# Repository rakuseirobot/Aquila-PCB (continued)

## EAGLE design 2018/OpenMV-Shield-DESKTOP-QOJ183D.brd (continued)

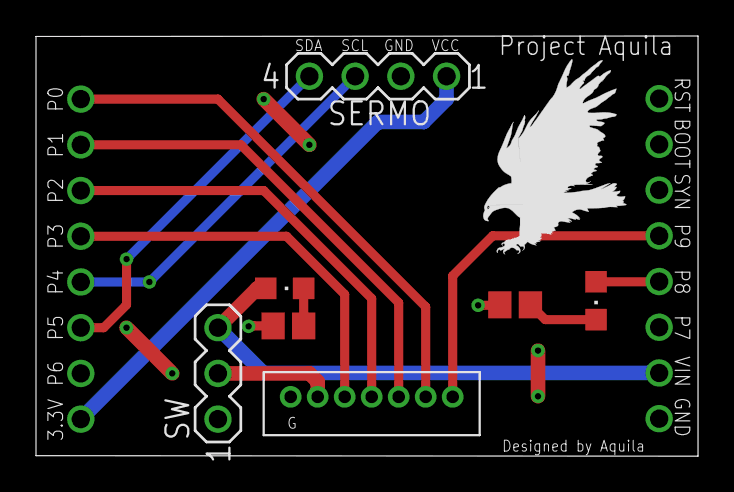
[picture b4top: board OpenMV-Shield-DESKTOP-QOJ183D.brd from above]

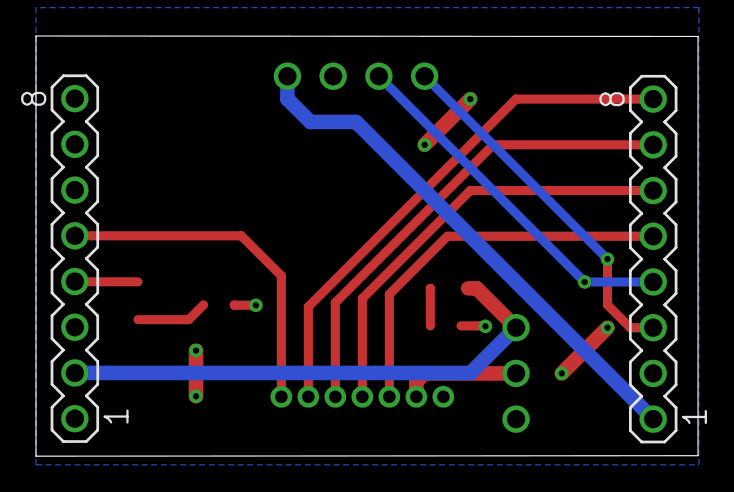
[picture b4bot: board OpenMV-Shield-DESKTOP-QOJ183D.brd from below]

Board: 2 copper layers, 36.8 x 23.3 mm, 10 parts (2 on the bottom side), 14 nets.

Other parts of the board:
U$1: EAGLE-PLC-8MM

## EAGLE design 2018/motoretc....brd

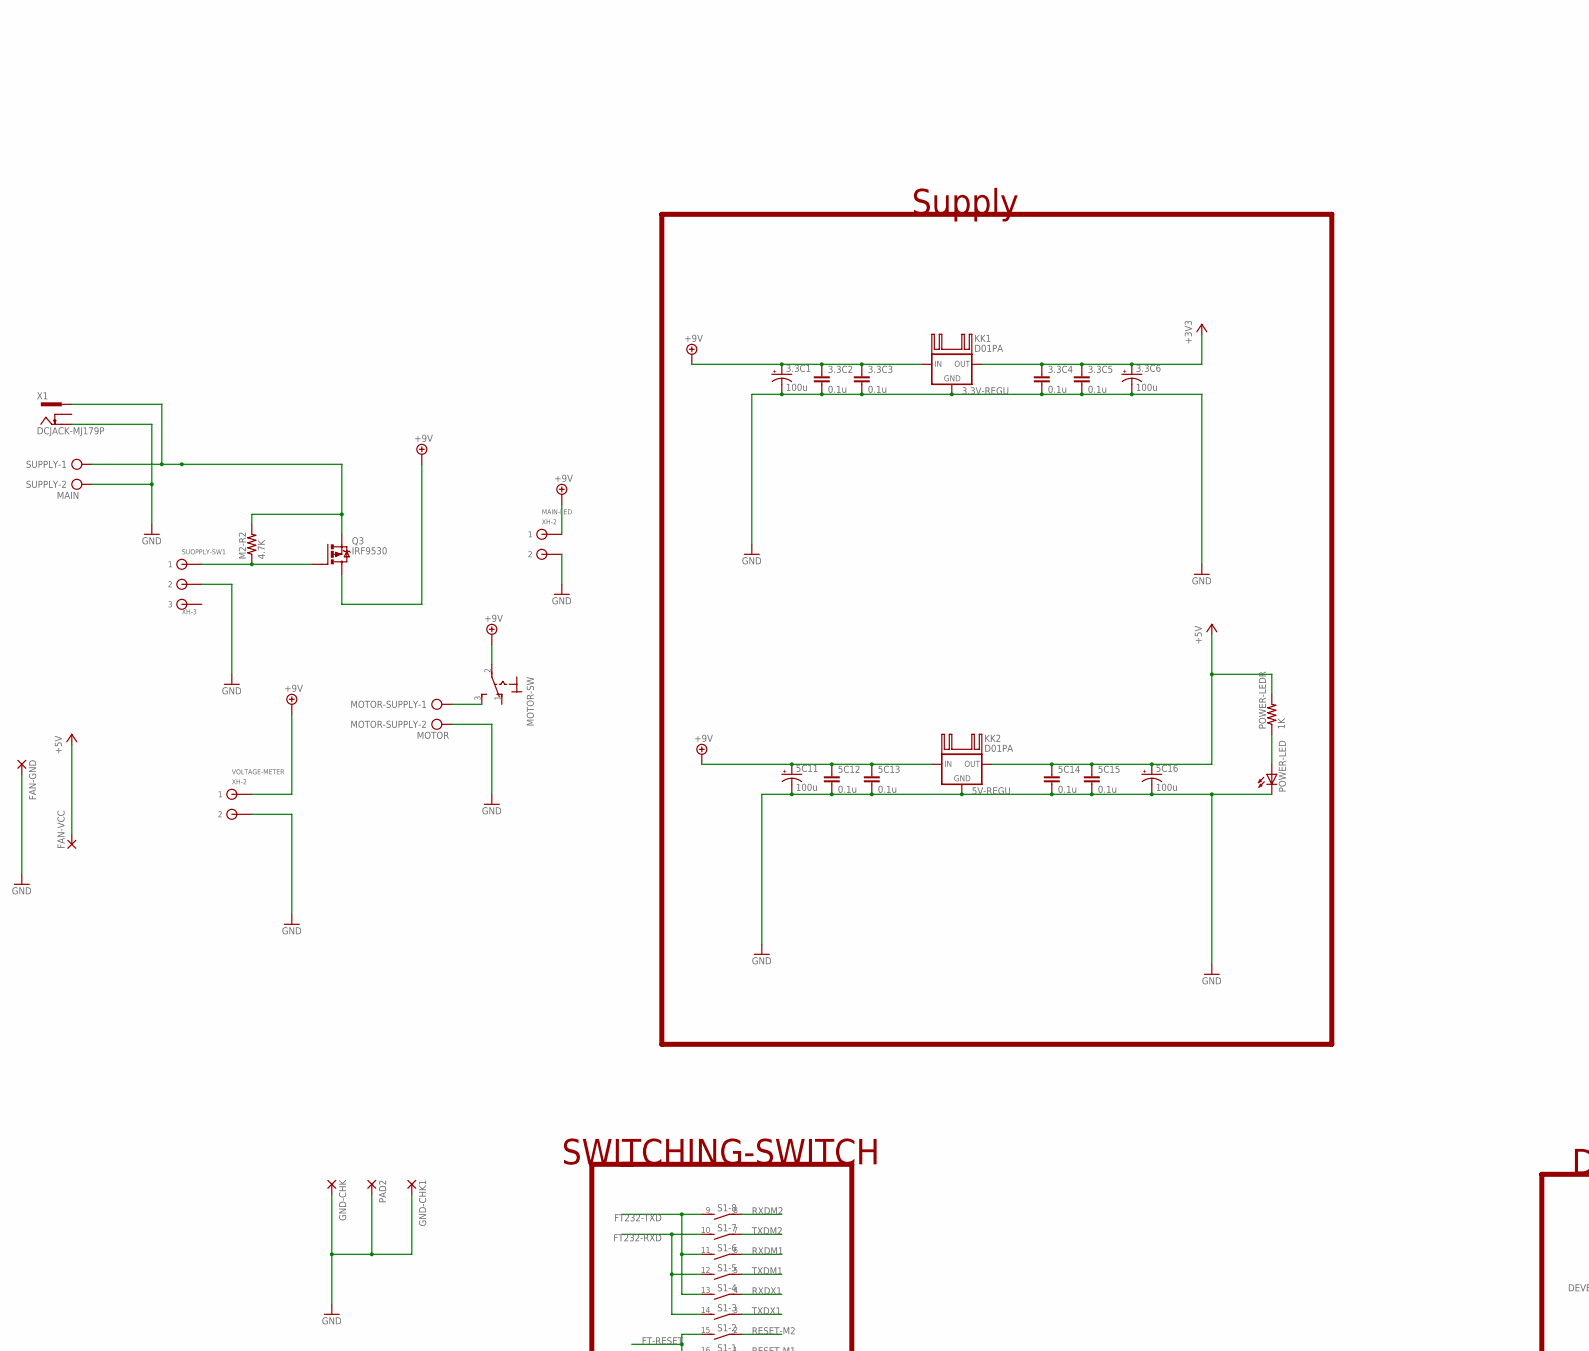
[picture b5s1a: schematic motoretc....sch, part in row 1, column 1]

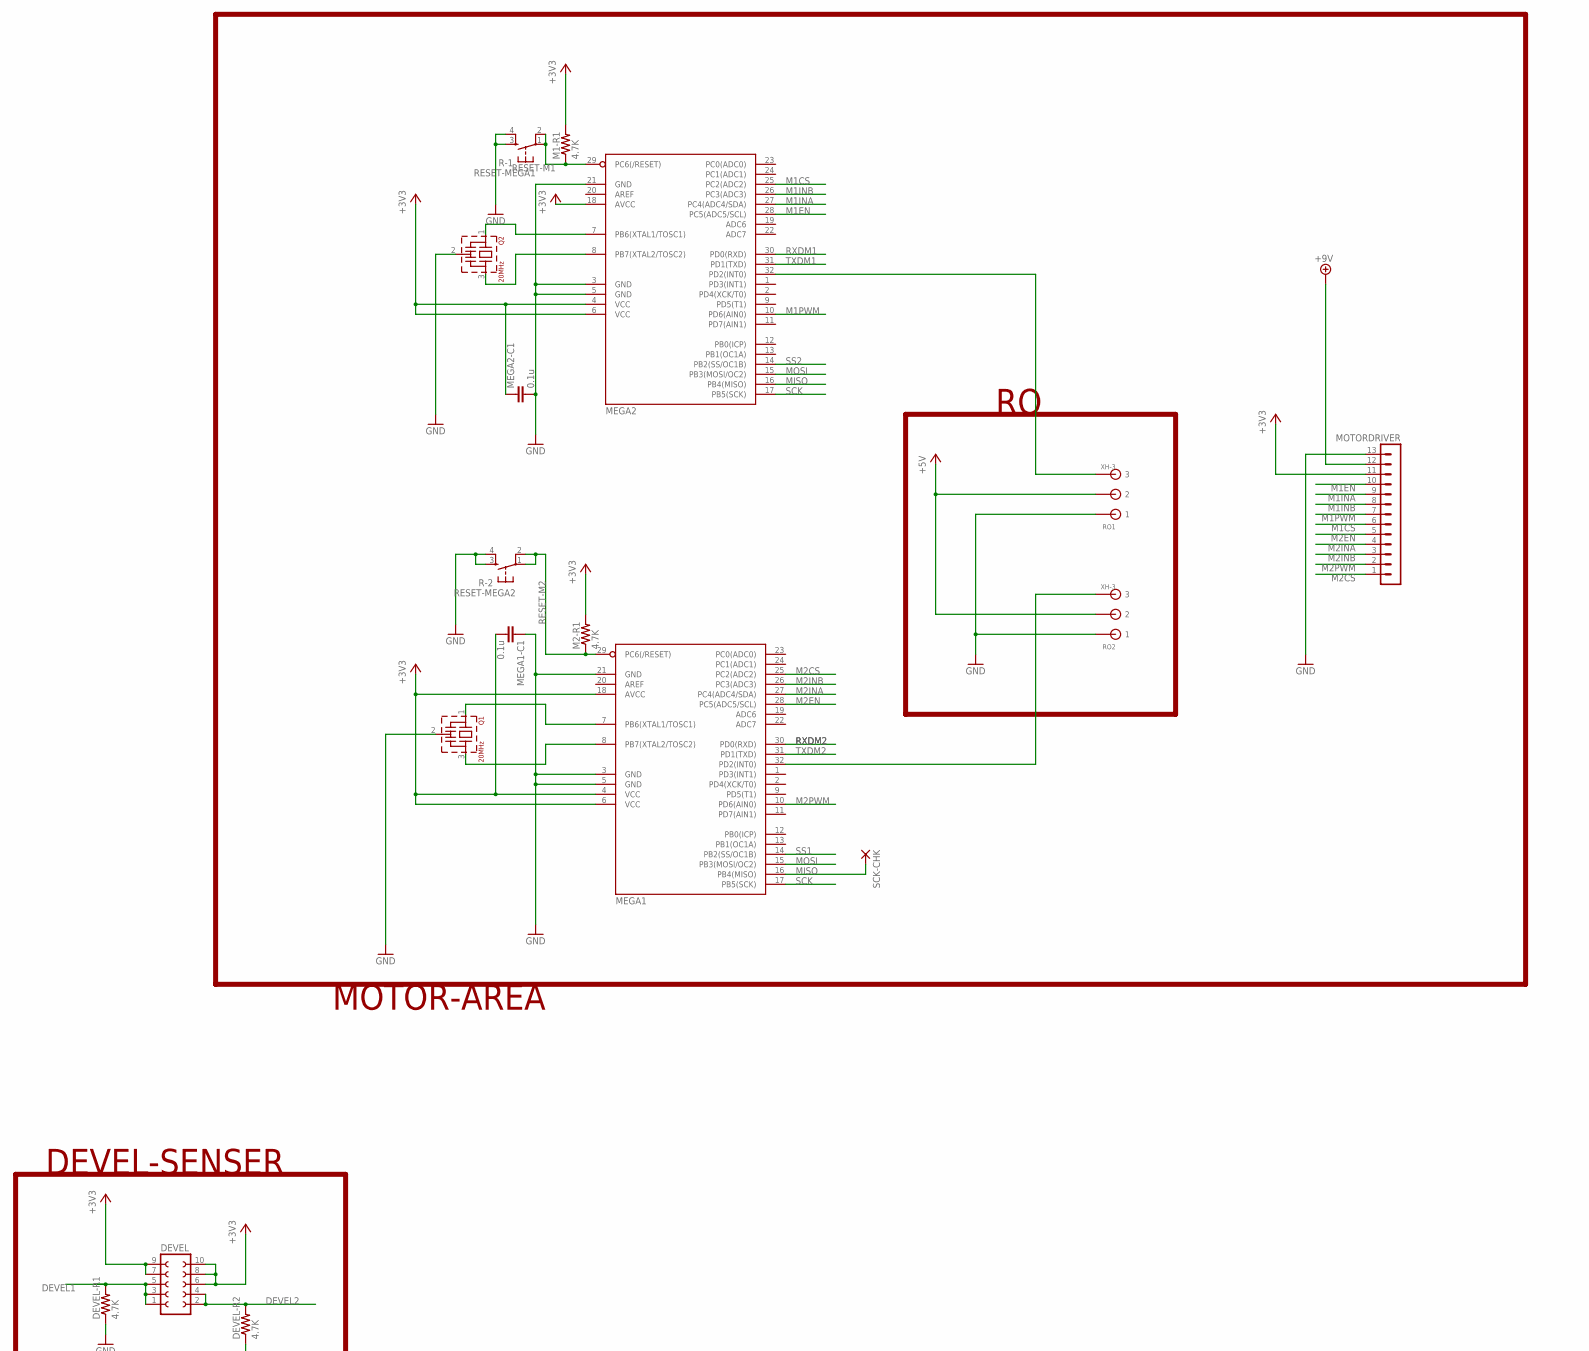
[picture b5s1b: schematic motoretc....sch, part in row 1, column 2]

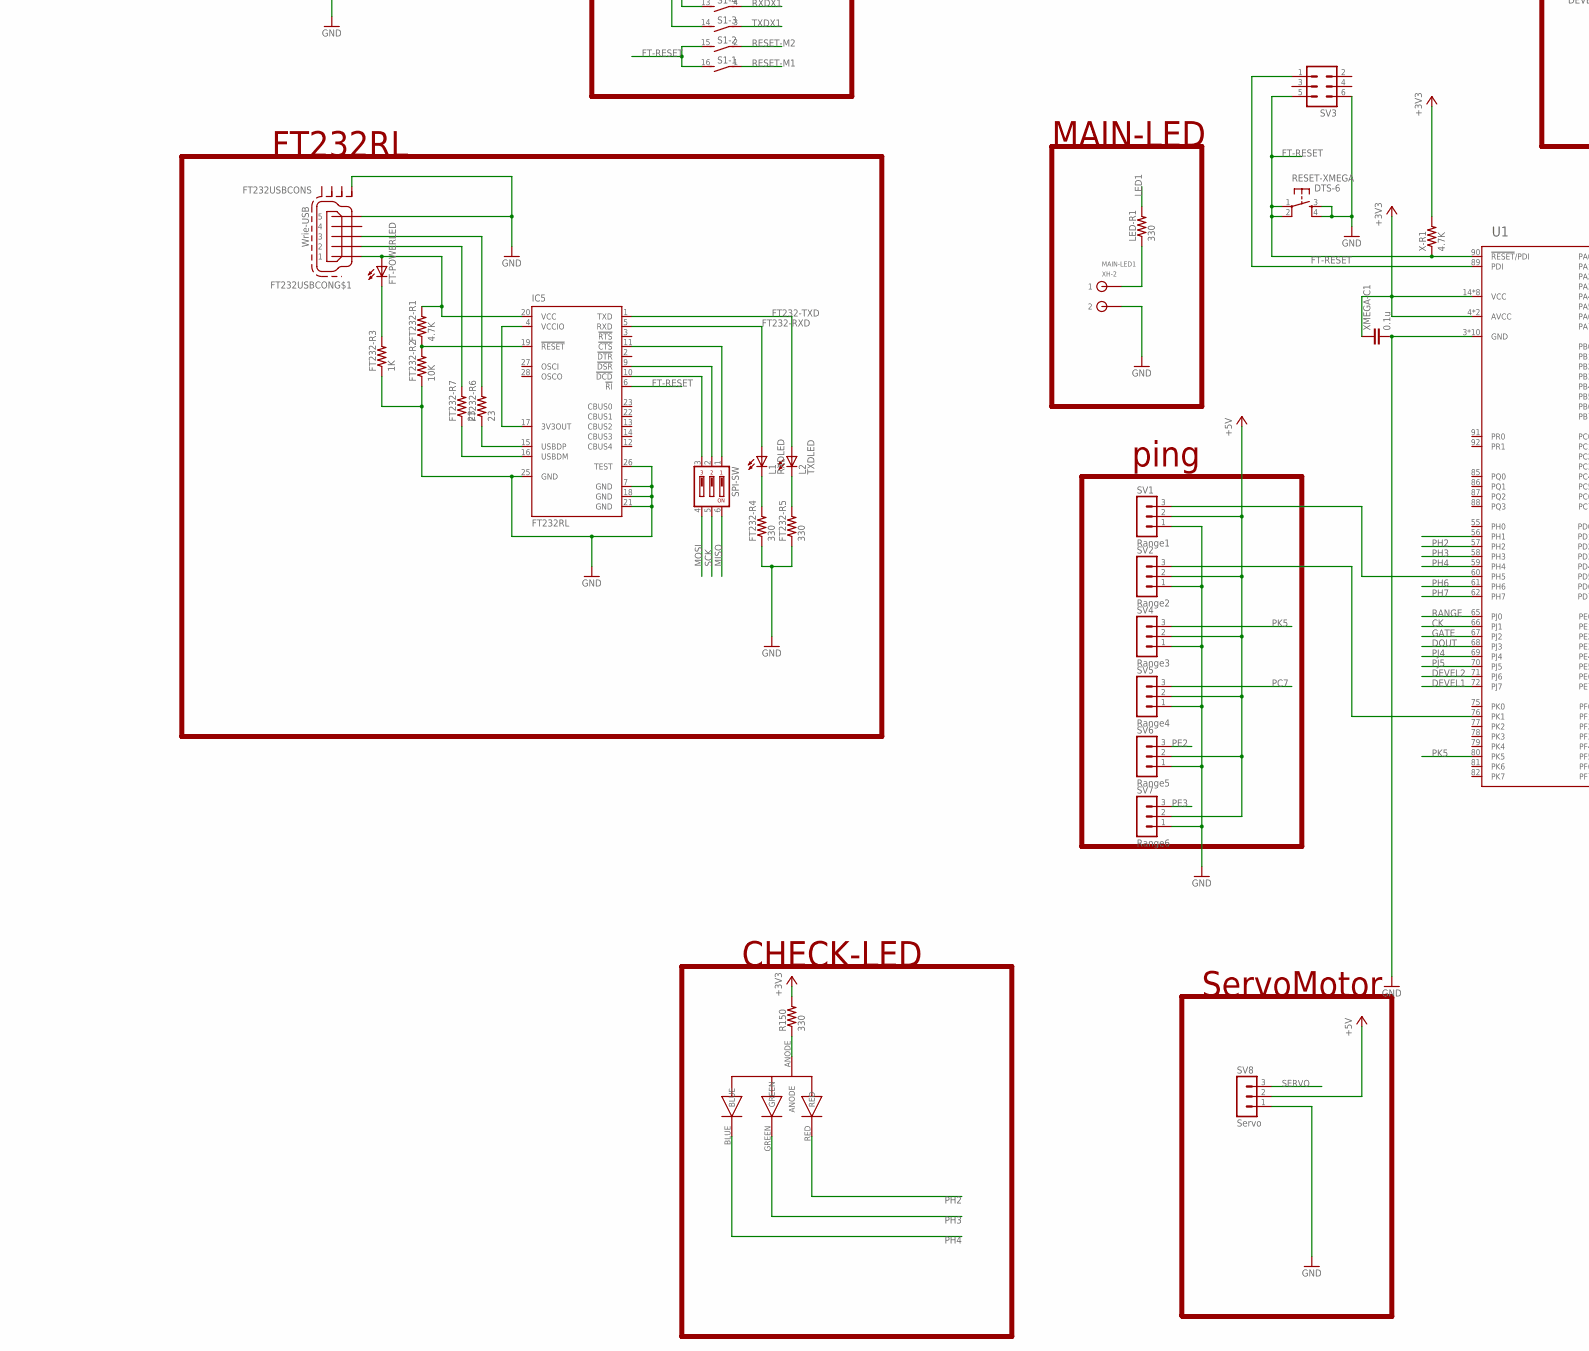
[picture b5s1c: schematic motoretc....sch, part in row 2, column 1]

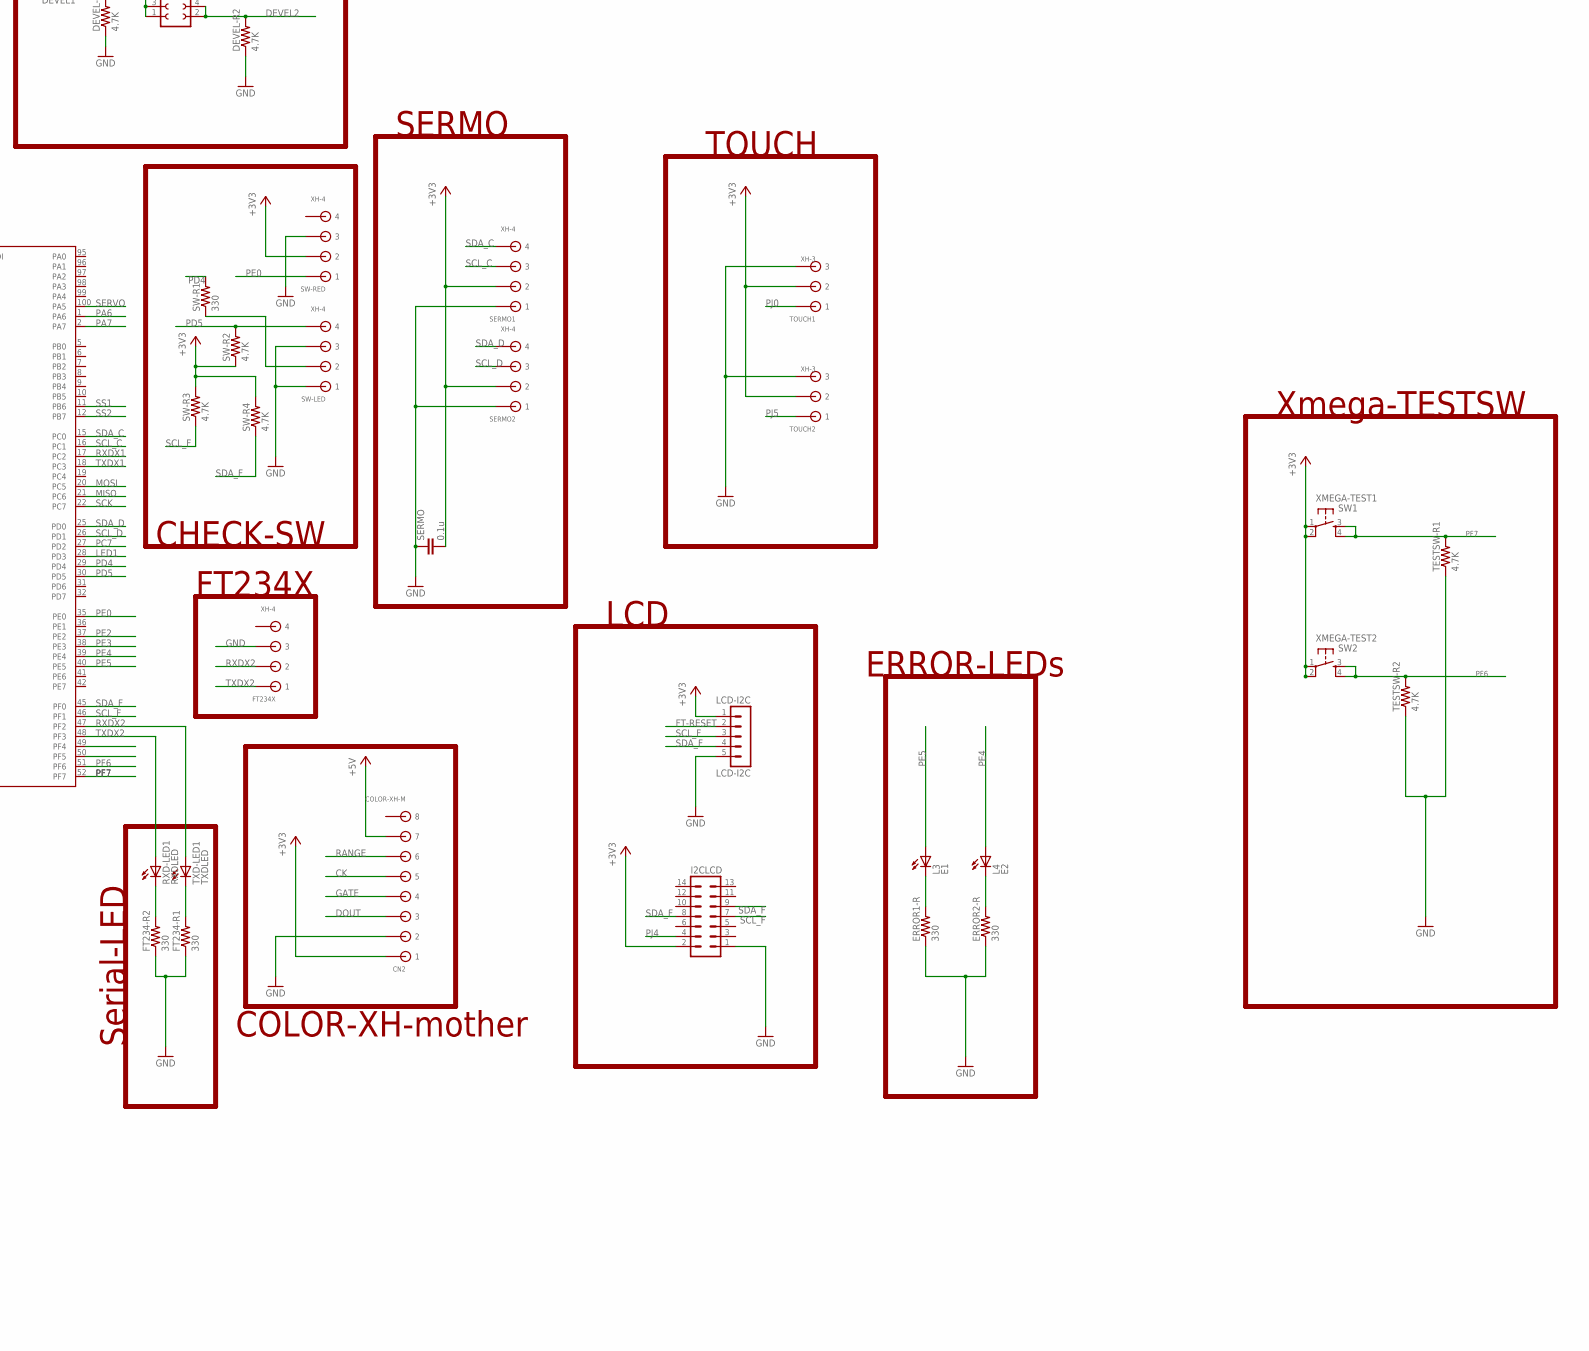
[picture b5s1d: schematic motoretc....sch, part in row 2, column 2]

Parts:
3.3C1, 3.3C6, 5C11, 5C16: 100u; E2,5-6
3.3C2, 3.3C3, 3.3C4, 3.3C5, 5C12, 5C13, 5C14, 5C15: 0.1u; C0805
3.3V-REGU, 5V-REGU: 78XXS
CHECKLED: OSTA71A1D-A
CN2: COLOR-XH-M; CON8
DEVEL: FE05-2
DEVEL-R1, DEVEL-R2: 4.7K; R0805
ERROR1-R, ERROR2-R: 330; R0805
FAN-GND: WIREPADSMD1,27-254; SMD1,27-2,54
FAN-VCC: WIREPADSMD1,27-254; SMD1,27-2,54
FT232-R1: 4.7K; R0805
FT232-R2: 10K; R0805
FT232-R3: 1K; R0805
FT232-R4, FT232-R5, FT234-R1, FT234-R2: 330; R0805
FT232-R6, FT232-R7: 23; R0805
FT232USBCON: Wrie-USB; 32005-201
FT234X: XH-4; CON4
FT-POWERLED: LEDCHIPLED_0805; CHIPLED_0805
GND-CHK, GND-CHK1: 2,15/1,0
I2CLCD: MA07-2
IC5: FT232RL; SSOP28
KK1, KK2: D01PA
L1: RXDLED; CHIPLED_0805
L2: TXDLED; CHIPLED_0805
L3: E1; LED5MM
L4: E2; LED5MM
LCD-I2C: LCD-I2C; MA05-1
LED-R1: 330; R0805
M1-R1, M2-R1, M2-R2: 4.7K; R0805
MAIN-LED, MAIN-LED1: XH-2; CON2
MEGA1, MEGA2: MEGA8-AI; TQFP32-08
MEGA1-C1, MEGA2-C1: 0.1u; C0805
MOTOR-SUPPLY: MOTOR; AK500/2
MOTOR-SW: 320-916
MOTORDRIVER: MA13-1
PAD2: SMD5; SMD2,54-5,08
POWER-LED: LEDCHIPLED_0805; CHIPLED_0805
POWER-LEDR: 1K; R0805
Q1, Q2: 20MHz; CSTLS_X
Q3: IRF9530; TO220BV
R150: 330; R0805
RESET-MEGA1: R-1; DTS-6
RESET-MEGA2: R-2; DTS-6
RESET-XMEGA: DTS-6
RO1, RO2: XH-3; CON3
RXD-LED1: RXDLED; CHIPLED_0805
S1: DIP08S
SCK-CHK: 2,15/1,0
SERMO: 0.1u; C0805
SERMO1, SERMO2: XH-4; CON4
SPI-SW: DIP03YL
SUOPPLY-SW1: XH-3; CON3
SUPPLY: MAIN; AK500/2
SV1: Range1; MA03-1
SV2: Range2; MA03-1
SV3: ML6
SV4: Range3; MA03-1
SV5: Range4; MA03-1
SV6: Range5; MA03-1
SV7: Range6; MA03-1
SV8: Servo; MA03-1
SW-LED: XH-4; CON4
SW-R1: 330; R0805
SW-R2, SW-R3, SW-R4: 4.7K; R0805
SW-RED: XH-4; CON4
TESTSW-R1, TESTSW-R2: 4.7K; R0805
TOUCH1, TOUCH2: XH-3; CON3
TXD-LED1: TXDLED; CHIPLED_0805
U1: ATXMEGA128A1U-AU; TQFP-100A-100
VOLTAGE-METER: XH-2; CON2
X1: DCJACK-MJ179P; MJ-179P
X-R1: 4.7K; R0805
XMEGA-C1: 0.1u; C0805
XMEGA-TEST1: SW1; DTS-6
XMEGA-TEST2: SW2; DTS-6

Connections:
+3V3: 3.3C4.1, 3.3C5.1, 3.3C6.+, 3.3V-REGU.OUT, CN2.P$1 (1), DEVEL.6, DEVEL.7, DEVEL.8, DEVEL.9, DEVEL.10, I2CLCD.2, LCD-I2C.1, M1-R1.2, M2-R1.2, MEGA1.4 (VCC), MEGA1.6 (VCC), MEGA1.18 (AVCC), MEGA1-C1.2, MEGA2.4 (VCC), MEGA2.6 (VCC), MEGA2.18 (AVCC), MEGA2-C1.1, MOTORDRIVER.11, R150.2, SERMO.2, SERMO1.P$2 (2), SERMO2.P$2 (2), SW-R2.1, SW-R3.2, SW-R4.2, SW-RED.P$2 (2), TOUCH1.P$2 (2), TOUCH2.P$2 (2), U1.4 (AVCC), U1.14 (VCC), U1.24 (VCC), U1.34 (VCC), U1.44 (VCC), U1.54 (VCC), U1.64 (VCC), U1.74 (VCC), U1.83 (VCC), U1.94 (AVCC), X-R1.2, XMEGA-C1.1, XMEGA-TEST1.1, XMEGA-TEST1.2, XMEGA-TEST2.1, XMEGA-TEST2.2
+5V: 5C14.1, 5C15.1, 5C16.+, 5V-REGU.OUT, CN2.P$7 (7), FAN-VCC.1, POWER-LEDR.2, RO1.P$2 (2), RO2.P$2 (2), SV1.2, SV2.2, SV4.2, SV5.2, SV6.2, SV7.2, SV8.2
+9V: 3.3C1.+, 3.3C2.1, 3.3C3.1, 3.3V-REGU.IN, 5C11.+, 5C12.1, 5C13.1, 5V-REGU.IN, MAIN-LED.P$1 (1), MOTOR-SW.2, MOTORDRIVER.12, Q3.D, VOLTAGE-METER.P$1 (1)
CK: CN2.P$5 (5), U1.66 (PJ1)
DEVEL1: DEVEL.1, DEVEL.3, DEVEL.5, DEVEL-R1.2, U1.72 (PJ7)
DEVEL2: DEVEL.2, DEVEL.4, DEVEL-R2.2, U1.71 (PJ6)
DOUT: CN2.P$3 (3), U1.68 (PJ3)
FT232-RXD: IC5.5 (RXD), L1.A, S1.10 (2), S1.12 (2), S1.14 (2)
FT232-TXD: IC5.1 (TXD), L2.A, S1.9 (2), S1.11 (2), S1.13 (2)
FT-POWERLED: FT232-R3.2, FT-POWERLED.C
FT-RESET: IC5.6 (!RI), LCD-I2C.2, RESET-XMEGA.1, RESET-XMEGA.2, S1.15 (2), S1.16 (2), SV3.5, U1.90 (!RESET!/PDI), X-R1.1
GATE: CN2.P$4 (4), U1.67 (PJ2)
GND: 3.3C1.-, 3.3C2.2, 3.3C3.2, 3.3C4.2, 3.3C5.2, 3.3C6.-, 3.3V-REGU.GND, 5C11.-, 5C12.2, 5C13.2, 5C14.2, 5C15.2, 5C16.-, 5V-REGU.GND, CN2.P$2 (2), DEVEL-R1.1, DEVEL-R2.1, ERROR1-R.1, ERROR2-R.1, FAN-GND.1, FT232-R2.1, FT232-R3.1, FT232-R4.1, FT232-R5.1, FT232USBCON.5, FT232USBCON.M1 (S1), FT234-R1.1, FT234-R2.1, FT234X.P$3 (3), GND-CHK.1, GND-CHK1.1, I2CLCD.1, IC5.7 (GND), IC5.18 (GND), IC5.21 (GND), IC5.25 (GND), IC5.26 (TEST), LCD-I2C.5, MAIN-LED.P$2 (2), MAIN-LED1.P$2 (2), MEGA1.3 (GND), MEGA1.5 (GND), MEGA1.21 (GND), MEGA1-C1.1, MEGA2.3 (GND), MEGA2.5 (GND), MEGA2.21 (GND), MEGA2-C1.2, MOTOR-SUPPLY.2, MOTORDRIVER.13, PAD2.1, POWER-LED.C, Q1.2 (VSS), Q2.2 (VSS), RESET-MEGA1.3, RESET-MEGA1.4, RESET-MEGA2.3, RESET-MEGA2.4, RESET-XMEGA.3, RESET-XMEGA.4, RO1.P$1 (1), RO2.P$1 (1), SERMO.1, SERMO1.P$1 (1), SERMO2.P$1 (1), SUOPPLY-SW1.P$2 (2), SUPPLY.2, SV1.1, SV2.1, SV3.6, SV4.1, SV5.1, SV6.1, SV7.1, SV8.1, SW-LED.P$1 (1), SW-LED.P$3 (3), SW-RED.P$3 (3), TESTSW-R1.1, TESTSW-R2.1, TOUCH1.P$3 (3), TOUCH2.P$3 (3), U1.3 (GND), U1.13 (GND), U1.23 (GND), U1.33 (GND), U1.43 (GND), U1.53 (GND), U1.63 (GND), U1.73 (GND), U1.84 (GND), U1.93 (GND), VOLTAGE-METER.P$2 (2), X1.2, XMEGA-C1.2
LED1: LED-R1.2, U1.28 (PD3)
M1CS: MEGA2.25 (PC2(ADC2)), MOTORDRIVER.6
M1EN: MEGA2.28 (PC5(ADC5/SCL)), MOTORDRIVER.10
M1INA: MEGA2.27 (PC4(ADC4/SDA)), MOTORDRIVER.9
M1INB: MEGA2.26 (PC3(ADC3)), MOTORDRIVER.8
M1PWM: MEGA2.10 (PD6(AIN0)), MOTORDRIVER.7
M2CS: MEGA1.25 (PC2(ADC2)), MOTORDRIVER.1
M2EN: MEGA1.28 (PC5(ADC5/SCL)), MOTORDRIVER.5
M2INA: MEGA1.27 (PC4(ADC4/SDA)), MOTORDRIVER.4
M2INB: MEGA1.26 (PC3(ADC3)), MOTORDRIVER.3
M2PWM: MEGA1.10 (PD6(AIN0)), MOTORDRIVER.2
MISO: MEGA1.16 (PB4(MISO)), MEGA2.16 (PB4(MISO)), SCK-CHK.1, SPI-SW.6, U1.21 (PC6)
MOSI: MEGA1.15 (PB3(MOSI/OC2)), MEGA2.15 (PB3(MOSI/OC2)), SPI-SW.4, U1.20 (PC5)
unnamed: SV1.3, U1.60 (PH5)
unnamed: MEGA2.32 (PD2(INT0)), RO1.P$3 (3)
unnamed: SV2.3, U1.76 (PK1)
unnamed: POWER-LED.A, POWER-LEDR.1
unnamed: MEGA1.32 (PD2(INT0)), RO2.P$3 (3)
unnamed: M2-R2.2, Q3.S, SUPPLY.1, X1.1
unnamed: SV3.1, U1.89 (PDI)
unnamed: FT232-R6.1, IC5.15 (USBDP)
unnamed: MEGA1.7 (PB6(XTAL1/TOSC1)), Q1.1
unnamed: MEGA1.8 (PB7(XTAL2/TOSC2)), Q1.3
unnamed: FT232-R6.2, FT232USBCON.3
unnamed: FT234-R2.2, RXD-LED1.C
unnamed: FT232-R7.1, IC5.16 (USBDM)
unnamed: CHECKLED.ANODE, R150.1
unnamed: FT234-R1.2, TXD-LED1.C
unnamed: IC5.11 (!CTS), SPI-SW.1
unnamed: SW-LED.P$2 (2), SW-R1.1
unnamed: MEGA2.7 (PB6(XTAL1/TOSC1)), Q2.1
unnamed: LED-R1.1, MAIN-LED1.P$1 (1)
unnamed: IC5.9 (!DSR), SPI-SW.2
unnamed: FT232-R7.2, FT232USBCON.2
unnamed: MEGA2.8 (PB7(XTAL2/TOSC2)), Q2.3
unnamed: FT232-R1.2, FT232USBCON.1, FT-POWERLED.A, IC5.20 (VCC)
unnamed: FT232-R1.1, FT232-R2.2, IC5.19 (!RESET)
unnamed: FT232-R4.2, L1.C
unnamed: FT232-R5.2, L2.C
unnamed: M2-R2.1, Q3.G, SUOPPLY-SW1.P$1 (1)
unnamed: IC5.10 (!DCD), SPI-SW.3
unnamed: IC5.4 (VCCIO), IC5.17 (3V3OUT)
unnamed: MOTOR-SUPPLY.1, MOTOR-SW.3 (S)
unnamed: ERROR1-R.2, L3.K (C)
unnamed: ERROR2-R.2, L4.K (C)
PA6: U1.1 (PA6)
PA7: U1.2 (PA7)
PC7: SV5.3, U1.27 (PD2)
PD4: SW-R1.2, U1.29 (PD4)
PD5: SW-LED.P$4 (4), SW-R2.2, U1.30 (PD5)
PE0: SW-RED.P$1 (1), U1.35 (PE0)
PE2: SV6.3, U1.37 (PE2)
PE3: SV7.3, U1.38 (PE3)
PE4: L4.A, U1.39 (PE4)
PE5: L3.A, U1.40 (PE5)
PF5: U1.50 (PF5)
PF6: TESTSW-R2.2, U1.51 (PF6), XMEGA-TEST2.3, XMEGA-TEST2.4
PF7: TESTSW-R1.2, U1.52 (PF7), XMEGA-TEST1.3, XMEGA-TEST1.4
PH2: CHECKLED.RED, U1.57 (PH2)
PH3: CHECKLED.GREEN, U1.58 (PH3)
PH4: CHECKLED.BLUE, U1.59 (PH4)
PH6: U1.61 (PH6)
PH7: U1.62 (PH7)
PJ0: TOUCH1.P$1 (1)
PJ4: I2CLCD.4, U1.69 (PJ4)
PJ5: TOUCH2.P$1 (1), U1.70 (PJ5)
PK5: SV4.3, U1.80 (PK5)
RANGE: CN2.P$6 (6), U1.65 (PJ0)
RESET-M1: M1-R1.1, MEGA2.29 (PC6(/RESET)), RESET-MEGA1.1, RESET-MEGA1.2, S1.1
RESET-M2: M2-R1.1, MEGA1.29 (PC6(/RESET)), RESET-MEGA2.1, RESET-MEGA2.2, S1.2 (1)
RXDM1: MEGA2.30 (PD0(RXD)), S1.6 (1)
RXDM2: MEGA1.30 (PD0(RXD)), S1.8 (1)
RXDX1: S1.4 (1), U1.17 (PC2)
RXDX2: FT234X.P$2 (2), TXD-LED1.A, U1.47 (PF2)
SCK: MEGA1.17 (PB5(SCK)), MEGA2.17 (PB5(SCK)), SPI-SW.5, U1.22 (PC7)
SCL_C: SERMO1.P$3 (3), U1.16 (PC1)
SCL_D: SERMO2.P$3 (3), U1.26 (PD1)
SCL_F: I2CLCD.7, LCD-I2C.3, SW-R3.1, U1.46 (PF1)
SDA_C: SERMO1.P$4 (4), U1.15 (PC0)
SDA_D: SERMO2.P$4 (4), U1.25 (PD0)
SDA_F: I2CLCD.8, I2CLCD.9, LCD-I2C.4, SW-R4.1, U1.45 (PF0)
SERVO: SV8.3, U1.100 (PA5)
SS1: MEGA1.14 (PB2(SS/OC1B)), U1.11 (PB6)
SS2: MEGA2.14 (PB2(SS/OC1B)), U1.12 (PB7)
TXDM1: MEGA2.31 (PD1(TXD)), S1.5 (1)
TXDM2: MEGA1.31 (PD1(TXD)), S1.7 (1)
TXDX1: S1.3 (1), U1.18 (PC3)
TXDX2: FT234X.P$1 (1), RXD-LED1.A, U1.48 (PF3)

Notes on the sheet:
ping
FT232RL
SERMO
MOTOR-AREA
LCD
TOUCH
COLOR-XH-mother
SWITCHING-SWITCH
MAIN-LED
DEVEL-SENSER
CHECK-SW
FT234X
CHECK-LED
Serial-LED
Supply
ServoMotor
ERROR-LEDs
Xmega-TESTSW

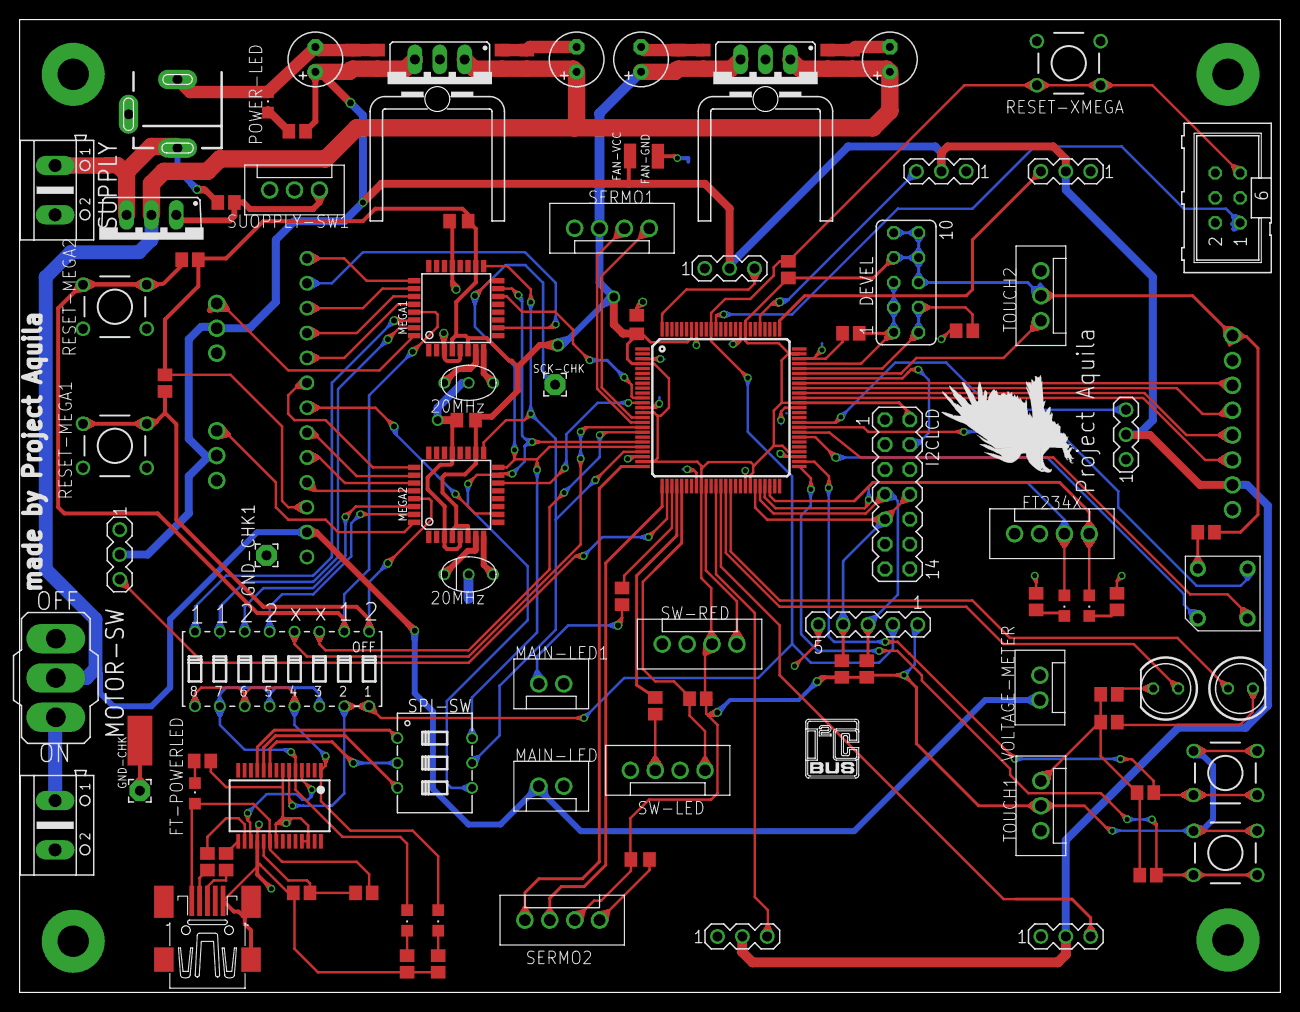
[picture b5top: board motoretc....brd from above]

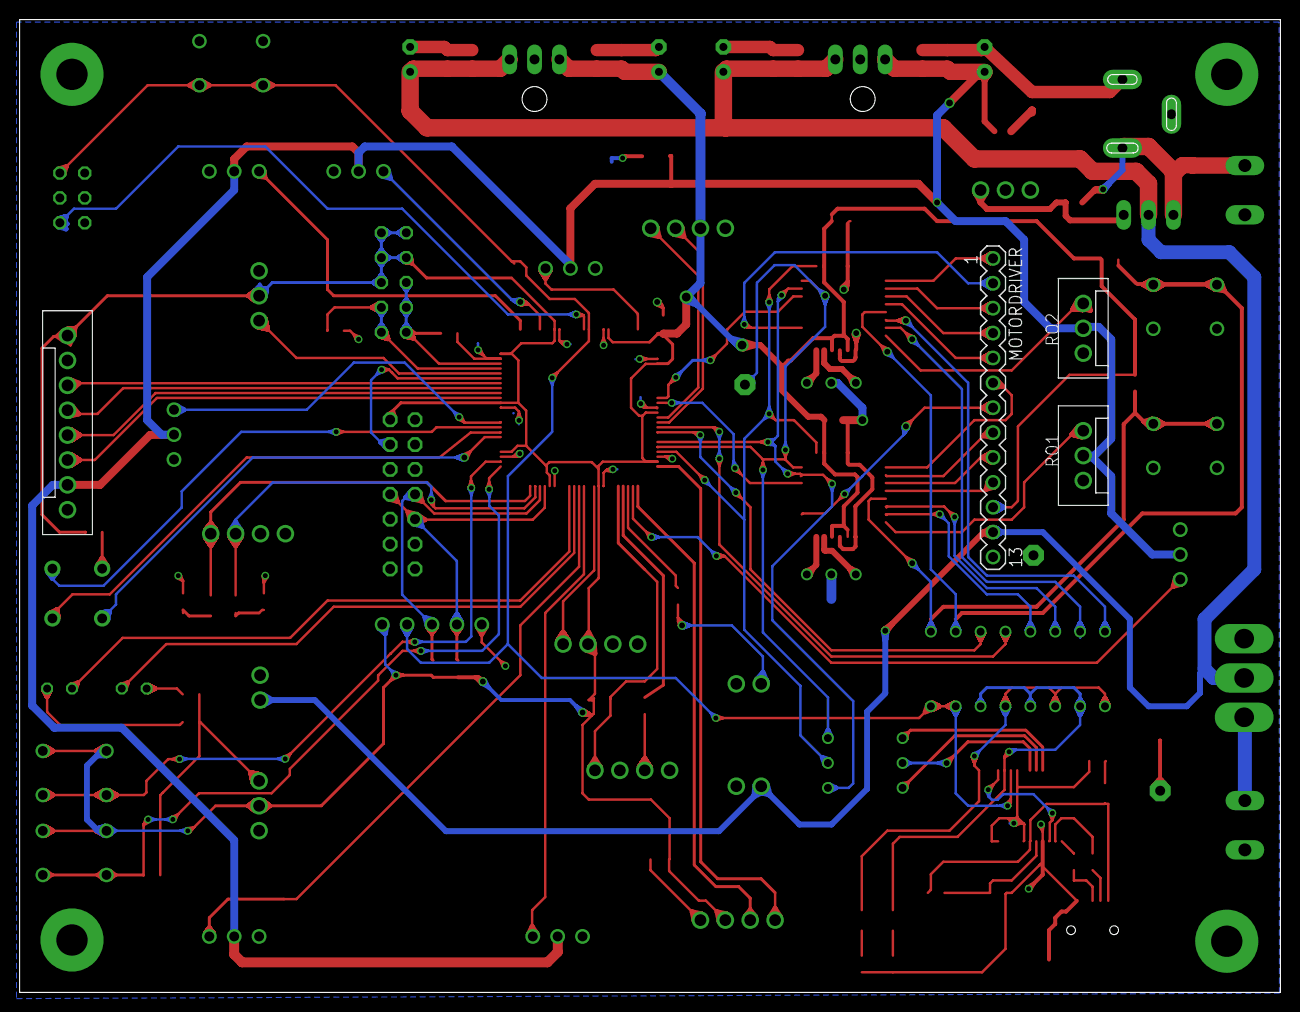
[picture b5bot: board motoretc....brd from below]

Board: 2 copper layers, 128.7 x 99.3 mm, 109 parts (4 on the bottom side), 95 nets.

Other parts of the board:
U$2: I2C
U$3: LOGO
U$4: EAGLE-PLC-10MM

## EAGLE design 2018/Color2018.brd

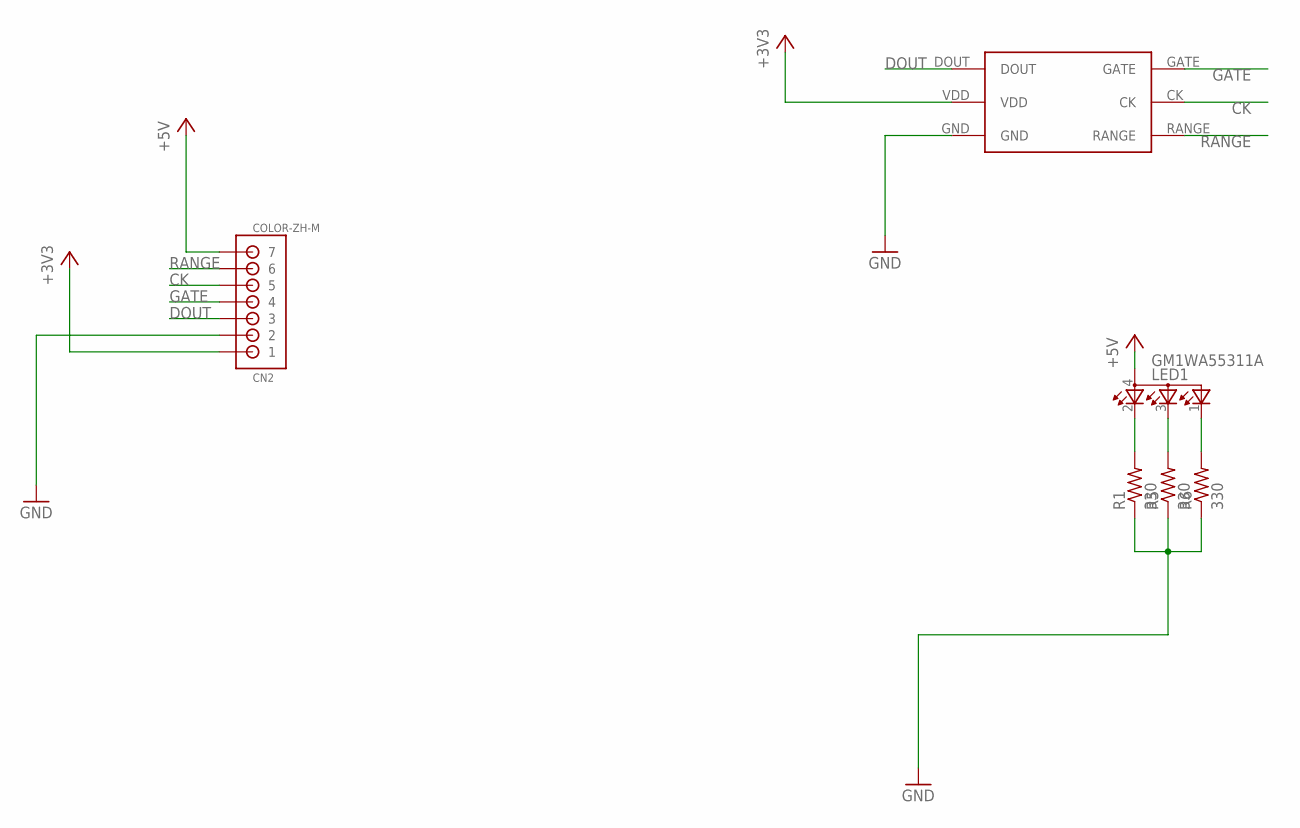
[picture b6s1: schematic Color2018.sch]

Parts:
CN2: COLOR-ZH-M; B7B-ZR
LED1: GM1WA55311A
R1, R5, R6: 330; R0805
U$1: S9706

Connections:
+3V3: CN2.1, U$1.VDD
+5V: CN2.7, LED1.4 (A)
CK: CN2.5, U$1.CK
DOUT: CN2.3, U$1.DOUT
GATE: CN2.4, U$1.GATE
GND: CN2.2, R1.1, R5.1, R6.1, U$1.GND
unnamed: LED1.2 (CRED), R1.2
unnamed: LED1.3 (CBLUE), R5.2
unnamed: LED1.1 (CGREEN), R6.2
RANGE: CN2.6, U$1.RANGE

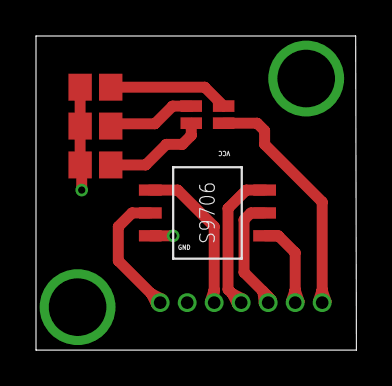
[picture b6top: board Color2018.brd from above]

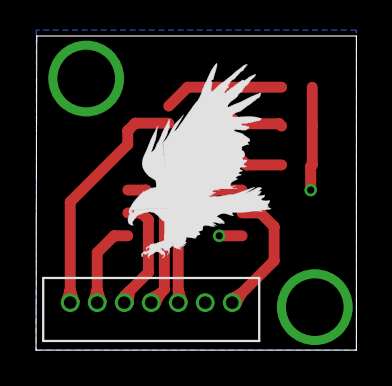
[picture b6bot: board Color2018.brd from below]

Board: 2 copper layers, 17.8 x 17.4 mm, 7 parts (2 on the bottom side), 10 nets.

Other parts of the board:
U$2: EAGLE-PLC-8MM
